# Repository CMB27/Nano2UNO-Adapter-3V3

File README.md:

# Nano2UNO Adapter 3V3

The Nano2UNO Adapter 3V3 is a circuit board to adapt 3.3V Arduino Nano boards the the Arduino UNO form factor.

All the IO pins on the Nano2UNO Adapter 3V3 are wired one to one from the Nano to the UNO form factor, no exceptions.
Pins A6 and A7 of the Nano are not connected because these pins are not present in the UNO form factor.

> [!NOTE]
> This design is distributed WITHOUT ANY EXPRESS OR IMPLIED WARRANTY, INCLUDING OF MERCHANTABILITY, SATISFACTORY QUALITY AND FITNESS FOR A PARTICULAR PURPOSE.
>
> The VCC pin (pin 2) on the ICSP header is connected to 5V.

> [!WARNING]
> Applying voltages higher than 3.3V to any I/O pin could damage any installed 3.3V Arduino Nano board.

### Compatibility
The Nano2UNO Adapter 3V3 should, in theory, be compatible with the following Arduino Nano boards:
- [Arduino Nano 33 IoT](https://store.arduino.cc/collections/boards-modules/products/arduino-nano-33-iot)
- [Arduino Nano 33 BLE](https://store.arduino.cc/collections/boards-modules/products/arduino-nano-33-ble)
- [Arduino Nano 33 BLE Sense](https://store.arduino.cc/collections/boards-modules/products/arduino-nano-33-ble-sense)
- [Arduino Nano 33 BLE Sense Rev2](https://store.arduino.cc/collections/boards-modules/products/nano-33-ble-sense-rev2)
- [Arduino Nano RP2040 Connect](https://store.arduino.cc/collections/boards-modules/products/arduino-nano-rp2040-connect)
- [Arduino Nano ESP32](https://store.arduino.cc/collections/boards-modules/products/nano-esp32)

### Documentation
- [Schematic](Nano2UNO-Adapter-3V3.pdf)
- [KiCAD Source Files](src)
- [STEP 3D Model](extras/Nano2UNO-Adapter-3V3.step)

## Components

### Circuit Board
#### Specifications
- Board Length: __68.58mm__
- Board Width: __53.34mm__
- Board Thickness: __1.6mm__
- Substrate Material: __FR4__
- Copper Layers: __2__
- Copper Thickness: __1oz__
- Soldermask Color: __Any__ (Blue Suggested)
- Smallest Hole Diameter: __0.8mm__
- Smallest Trace Width: __0.2mm__ (7.8mil)
- Smallest Trace Spacing: __0.2mm__ (7.8mil)

#### Suppliers
Below are some circuit board manufacturers I have used in the past.
Generally you will need to upload the upload the [gerber and drill files](gerbers) to their websites in a .zip folder.

- [OSH Park](https://oshpark.com) is a US based circuit board fabrication service.
  They tend to be more expensive than other manufacturers and the number of options they give you are limited (If you use this manufacturer, I hope you like purple).

- [Seeed Studio Fusion](https://www.seeedstudio.com/fusion_pcb.html) makes circuit boards in China.
  They have a lot of options when ordering; please refer to the [specifications](#specifications) above when making your choices.
  They do have a circuit board assembly service as well, but I am not especially familiar with it.

### Purchase Components

| References | Quantity | Manufacturer | Part Number    | Description                     | Notes                                                                                  |
|------------|---------:|--------------|----------------|---------------------------------|----------------------------------------------------------------------------------------|
| C1, C2     |        2 | Panasonic    | ECE-A1HKS100   | 10uF X7R Through-Hole Capacitor | These are use as decoupling capacitors for the 5V DC DC converter.                     |
| D1         |        1 | Vishay       | SB260S-E3/54   | DO-41 Diode                     | This provides reverse voltage protection on the VIN pin and barrel jack.               |
| J1, J3     |        2 | Samtec       | ESW-108-33-L-S | 1x8 Socket Header               | These are extended socket headers that make up part of the Arduino UNO interface.      |
| J2         |        1 | Samtec       | ESW-110-33-L-S | 1x10 Socket Header              | This is an extended socket header that makes up part of the Arduino UNO interface.     |
| J4         |        1 | Samtec       | ESW-106-33-L-S | 1x6 Socket Header               | This is an extended socket header that makes up part of the Arduino UNO interface.     |
| J5, J6     |        2 | Sullins      | PPPC151LFBN-RC	| 1x15 Socket Header              | These are typical, 8.5mm tall, socket headers that make up the Arduino Nano interface. |
| J7         |        1 | TSW/Samtec   | TSW-103-15-L-D | 2x3 Pin Header                  | This is an extended pin header that makes up part of the Arduino UNO interface.        |
| J8         |        1 | CUI          | PJ-102A        | 2.0mm ID, 5.5mm OD Barrel Jack  | This is a pretty common barrel jack.                                                   |
| SW1        |        1 | TE           | 1825910-6      | 6mm Pushbutton Switch           | This is a generic 6mm pushbutton switch.                                               |
| U1         |        1 | RECOM        | R-78K5.0-0.5   | 5V DC DC Converter              | This DC DC converter has an input voltage range of 6.5 - 36V.                          |

#### Suppliers
Below are some electronics suppliers I have used in the past:

- [Digi-Key](https://www.digikey.com/) is my usual go-to supplier for electronic components.
  Their website makes it pretty easy to sort through parts.

- [Mouser](https://www.mouser.com/) is very similar to Digi-Key in a lot of ways.
  They sometimes have better pricing, and they have excellent customer support.

- [Newark](https://www.newark.com/) tends to have a bit different selection than Digi-Key and Mouser, especially in the area of connectors.

- [Octopart](https://octopart.com/) is not a supplier per se; it is essenitally an electronic component search engine.
  This can be a very helpful tool when looking for parts, especially somewhat unusual ones, like extended socket headers.

All of these suppliers have a feature on their respective websites where you can upload a spreadsheet file, such as [Nano2UNO-Adapter-3V3-BOM.csv](Nano2UNO-Adapter-3V3-BOM.csv), to populate the cart or find parts.

Last I checked, it is not possible to order all the components needed to build a Nano2UNO Adapter 3V3 from just one of these suppliers. Multiple orders will be needed.

## Assembly

### Tools and Supplies
| Item              | Optional | Notes                                                                                                                                              |
|-------------------|----------|----------------------------------------------------------------------------------------------------------------------------------------------------|
| Soldering Iron    | No       | Make sure you use a good quality soldering iron. A poor quality soldering iron will give you a miserable soldering experience.                     |
| Flush Cutters     | No       | These are used to trim component leads.                                                                                                            |
| Flux Core Solder  | No       | Leaded solder is easier to work with, but lead-free solder is better for the environment.                                                          |
| Solder Flux       | Yes      | Extra flux will make the solder flow better. I don't usually use it when through-hole soldering, but it can be helpful.                            |
| Solder Wick       | Yes      | This is used to remove solder from places you don't want it.                                                                                       |
| Solder Sucker     | Yes      | If you need to de-solder a component, this, along with solder wick, is the tool you want. This can quickly remove most of the solder from a joint. |
| Arduino Shield    | Yes      | This can be used to hold the stacking socket headers in place while being assembled.                                                               |
| Isopropyl Alcohol | Maybe    | This is used to remove flux. It is not needed if you are using no-clean flux.                                                                      |
| Dish Soap         | Maybe    | This is used to remove flux residue. It is not needed if you are using no-clean flux.                                                              |

> **Note on Flux**  
> Traditional flux if left on the assembled circuit board could cause some serious issues.
> It can potentially cause shorts or significant [parasitic capacitance](https://en.wikipedia.org/wiki/Parasitic_capacitance).
> It is also somewhat corrosive and can, over time, damage your circuit board.
> This sort of flux must be cleaned off the board after assembly.
> 
> To address these issues there are no-clean fluxes, that can be left on the circuit board assembly and are unlikly to cause these issues.
> There are also water-soluble fluxes that can be cleaned off with hot water, though I have found that some isopropyl alcohol can speed up the process.
> There are also fluxes that are both no-clean and water soluble; this is what I like to use.

### Assembly Steps
All the components are placed on the front side of the board and solderd on the back side of the board.
These steps go through soldering each component, starting with the shortest.

> The [interactive HTML BOM](https://github.com/CMB27/Nano2UNO-Adapter-3V3/blob/main/extras/Nano2UNO-Adapter-3V3-interactive-BOM.html) may be helpful to you in this process.
> It graphically shows where each component goes on the board.
> You will need to download it in order to view it; GitHub does not render HTML files in repositories.

#### 1. D1 (Diode)
- Bend the diode leads so that the part will fit in the footprint.
- Place the diode, ensuring that the side with the line closest to it (the cathode) is facing the squarish pad.
- Bend the diode leads on the backside of the board to ensure the diode remains in place when soldering.
- Solder the leads to the pads.
- Trim the leads using flush cutters.

#### 2. SW1 (Pushbutton Switch)
- Place the switch; it should stay in place.
- Solder the leads to the board.

#### 3. C1-C2 (Capacitors)
- Place the capacitors, ensuring that the `-` symbol on the capacitors is facing away from the `+` symbols on the board.
  For the capacitors the, the positive lead goes through the squarish pad and the negative lead goes through the circular pad.
- Bend the capacitor leads on the backside of the board to ensure the capacitors stay in place.
- Solder the capacitor leads.
- Trim the leads.

#### 4. J5-J6 (Arduino Nano Socket)
- If you have an Arduino Nano board, place the socket headers on the Nano's pins, then place the socket header pins through the holes on the Nano2UNO circuit board.
  This will ensure your Nano board will line up with the sockets once they are soldered in place.
  If you do not have an Arduino Nano board on hand, place the socket header pins as precisely as you can.
- Carefully flip the board over the board, holding the socket headers in place.
  This can be difficult; it may be necessary to solder each socket header one at a time.
- Tack solder the end pins of the socket headers.
- Check that the socket headers are straight and seated correctly.
  If necessary remelt the solder joints to adjust the socket headers. (This is where flux can be nice.)
- Once the headers are straight, solder the remaining pins. I usually go every other pin to avoid heat build up, then go back soldering the pins I skipped.
- If you used an Arduino Nano board to place the sockets, remove it now.

#### 5. U1 (DC DC Converter)
- Place the DC DC converter module.
- Tack solder one pin. I like to solder the middle pin.
- Check that the component is straight and seated correctly.
  Remelt the tack joint to make corrections if necessary.
- Solder the remaining two pins.

#### 6. J8 (Barrel Jack)
- Place the barrel Jack.
- Tack solder the pin near the middle of the component.
- Check that the part is straight and seated correctly.
- Solder the remaining pins.

#### 7. J7 (ICSP Header)
- Place the pin header.
- Tack solder one pin. I like to solder one of the corners.
  Be careful when soldering this component; it has a lot of exposed metal that can burn you when heated by a soldering iron.
- Check that the part is straight and seated correctly.
- Solder the remaining pins.

#### 8. J1-J4 (Arduino UNO Interface)
- If you have a shield for the Arduino UNO, place the socket headers on its pins, then place the socket header pins through the holes on the Nano2UNO circuit board.
  This will make it easier and faster to install the sockets.
  If you don't have a shield you will likely need to install the sockets one at a time.
- Carefully flip the board over the board, holding the socket headers in place.
- Tack solder the end pins of the socket headers.
- Check that the socket headers are straight and seated correctly.
- Once the headers are straight, solder the remaining pins.
- If you used a shield, remove it now.

#### 9. Clean Flux Off Board  
_If you used no-clean flux, you can skip this step._

> [!NOTE]
> This step was written with water-soluble flux in mind.  
> If you used non-water-soluble flux, you may need to use a different cleaning process.

- Use isopropyl alcohol with a toothbrush to remove the bulk of the flux.
- Clean the board with dish soap and warm water using the same toothbrush.
- Dry the board thoroughly. I like to use compressed air for this step.

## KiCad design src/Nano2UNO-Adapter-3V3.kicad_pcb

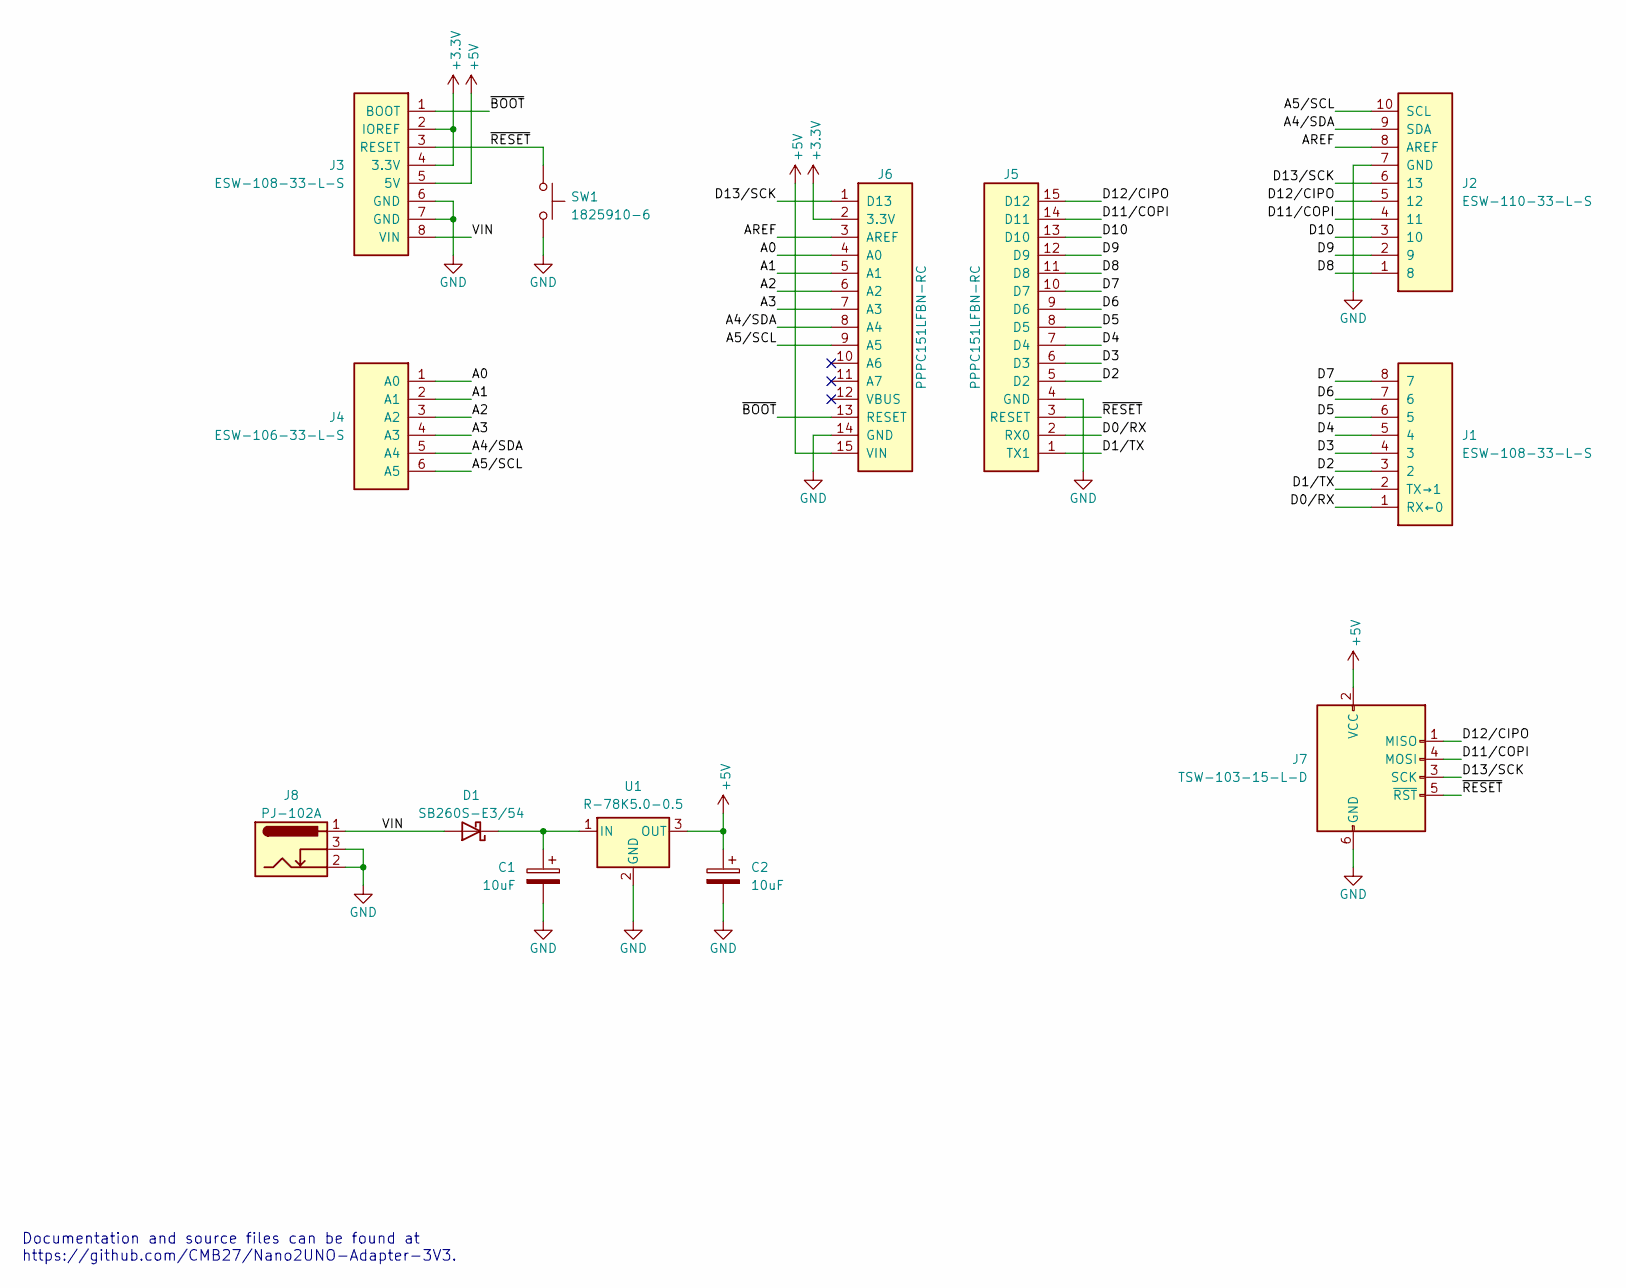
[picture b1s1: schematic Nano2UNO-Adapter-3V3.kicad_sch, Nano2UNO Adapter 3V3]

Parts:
C1, C2: 10uF; CP_Radial_D6.3mm_P2.50mm; Part Number ECE-A1HKS100
D1: SB260S-E3/54; D_DO-41_SOD81_P10.16mm_Horizontal; Part Number SB260S-E3/54
J1: ESW-108-33-L-S; PinSocket_1x08_P2.54mm_Vertical_UNO_Digital_1; Part Number ESW-108-33-L-S
J2: ESW-110-33-L-S; PinSocket_1x10_P2.54mm_Vertical_UNO_Digital_2; Part Number ESW-110-33-L-S
J3: ESW-108-33-L-S; PinSocket_1x08_P2.54mm_Vertical_UNO_Power; Part Number ESW-108-33-L-S
J4: ESW-106-33-L-S; PinSocket_1x06_P2.54mm_Vertical_UNO_Analog; Part Number ESW-106-33-L-S
J5: PPPC151LFBN-RC; PinSocket_1x15_P2.54mm_Vertical_Nano_1; Part Number PPPC151LFBN-RC
J6: PPPC151LFBN-RC; PinSocket_1x15_P2.54mm_Vertical_Nano_2; Part Number PPPC151LFBN-RC
J7: TSW-103-15-L-D; PinHeader_2x03_P2.54mm_Vertical_UNO_ICSP; Part Number TSW-103-15-L-D
J8: PJ-102A; BarrelJack_CUI_PJ-102A_Horizontal; Part Number PJ-102A
SW1: 1825910-6; SW_PUSH_6mm_Reset; Part Number 1825910-6
U1: R-78K5.0-0.5; Part Number R-78K5.0-0.5

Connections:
+3V3: J3.2 (IOREF), J3.4 (3.3V), J6.2 (3.3V)
+5V: C2.1, J3.5 (5V), J6.15 (VIN), J7.2 (VCC), U1.3 (OUT)
/A0: J4.1 (A0), J6.4 (A0)
/A1: J4.2 (A1), J6.5 (A1)
/A2: J4.3 (A2), J6.6 (A2)
/A3: J4.4 (A3), J6.7 (A3)
/A4/SDA: J2.9 (SDA), J4.5 (A4), J6.8 (A4)
/A5/SCL: J2.10 (SCL), J4.6 (A5), J6.9 (A5)
/AREF: J2.8 (AREF), J6.3 (AREF)
/D0/RX: J1.1 (RX←0), J5.2 (RX0)
/D1/TX: J1.2 (TX→1), J5.1 (TX1)
/D2: J1.3 (2), J5.5 (D2)
/D3: J1.4 (3), J5.6 (D3)
/D4: J1.5 (4), J5.7 (D4)
/D5: J1.6 (5), J5.8 (D5)
/D6: J1.7 (6), J5.9 (D6)
/D7: J1.8 (7), J5.10 (D7)
/D8: J2.1 (8), J5.11 (D8)
/D9: J2.2 (9), J5.12 (D9)
/D10: J2.3 (10), J5.13 (D10)
/D11/COPI: J2.4 (11), J5.14 (D11), J7.4 (MOSI)
/D12/CIPO: J2.5 (12), J5.15 (D12), J7.1 (MISO)
/D13/SCK: J2.6 (13), J6.1 (D13), J7.3 (SCK)
/VIN: D1.2 (A), J3.8 (VIN), J8.1
/~BOOT: J3.1 (BOOT), J6.13 (RESET)
/~RESET: J3.3 (RESET), J5.3 (RESET), J7.5 (~RST), SW1.2
GND: C1.2, C2.2, J2.7 (GND), J3.6 (GND), J3.7 (GND), J5.4 (GND), J6.14 (GND), J7.6 (GND), J8.2, J8.3, SW1.1, U1.2 (GND)
unnamed: C1.1, D1.1 (K), U1.1 (IN)

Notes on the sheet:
Documentation and source files can be found at https://github.com/CMB27/Nano2UNO-Adapter-3V3.

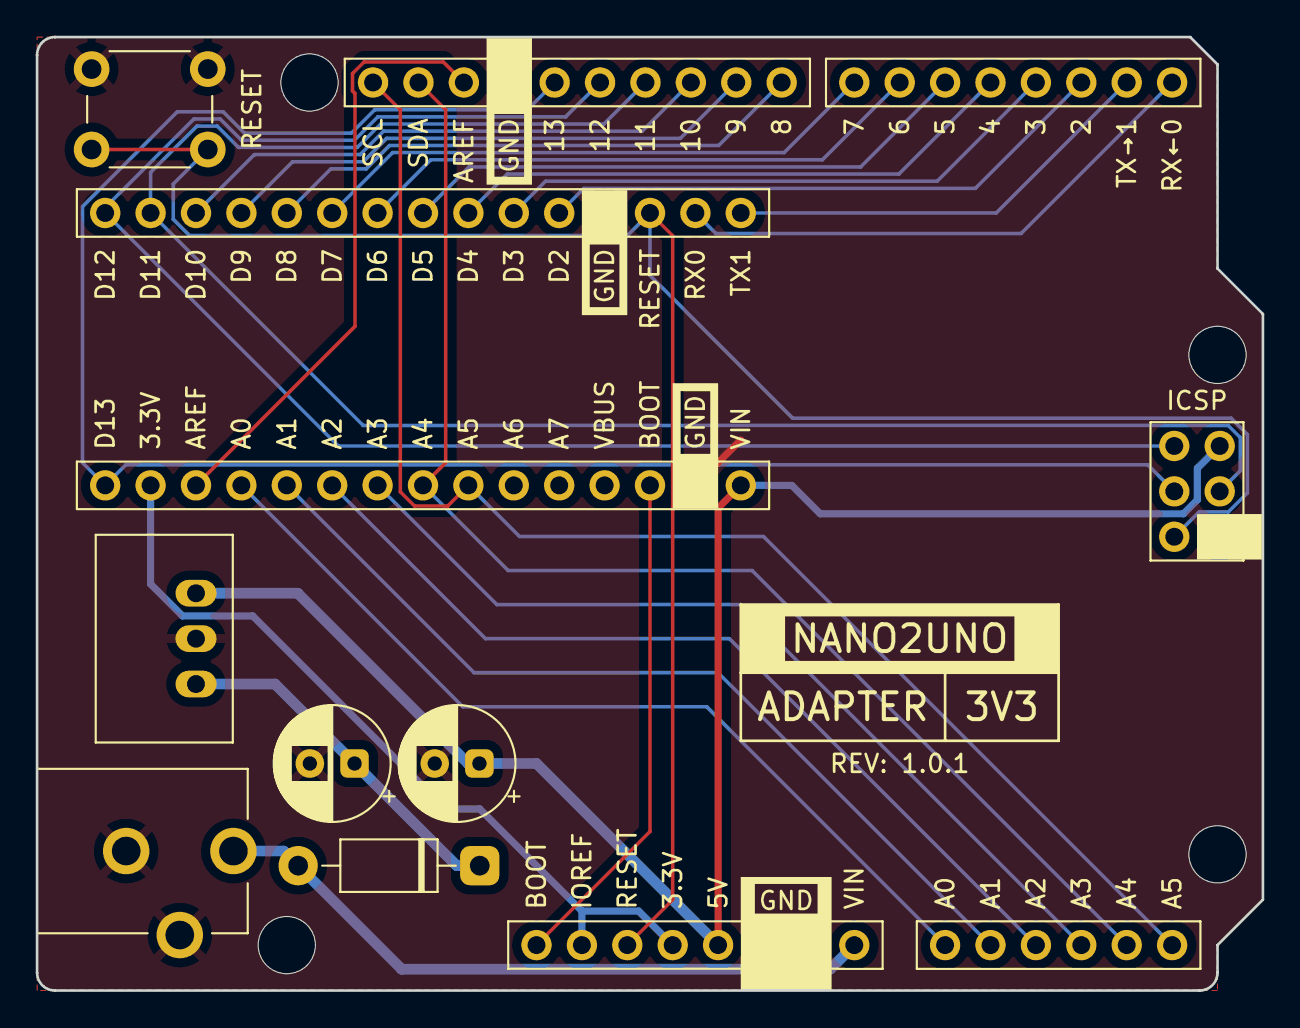
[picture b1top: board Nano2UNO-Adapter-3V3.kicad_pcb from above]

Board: 2 copper layers, 68.6 x 53.3 mm, 17 parts (0 on the bottom side), 28 nets.

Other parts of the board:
MH1, MH2, MH3, MH4: MountingHole_3.2mm

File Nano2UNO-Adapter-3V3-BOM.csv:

"Item","References","Quantity","Manufacturer","Part Number","Description"

"1","","1","","","Nano2UNO Adapter 3V3 Bare Circuit Board"
"2","C1, C2","2","Panasonic","ECE-A1HKS100 ","10uF X7R Through-Hole Capacitor"
"3","D1","1","Vishay","SB260S-E3/54","DO-41 Diode"
"4","J1, J3","2","Samtec","ESW-108-33-L-S","1x8 Socket Header"
"5","J2","1","Samtec","ESW-110-33-L-S","1x10 Socket Header"
"6","J4","1","Samtec","ESW-106-33-L-S","1x6 Socket Header"
"7","J5, J6","2","Sullins","PPPC151LFBN-RC","1x15 Socket Header"
"8","J7","1","TSW/Samtec","TSW-103-15-L-D","2x3 Pin Header"
"9","J8","1","CUI","PJ-102A","2.0mm ID, 5.5mm OD Barrel Jack"
"10","SW1","1","TE","1825910-6","6mm Pushbutton Switch"
"11","U1","1","RECOM","R-78K5.0-0.5","5V DC DC Converter"

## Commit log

2023-12-06 Increased the font size of the comments and dimensions.
2023-12-06 Genereated images of board.
2023-12-06 Removed the board PDF. Updated the schematic PDF.
2023-12-06 Updated README.
2023-12-06 Updated README. Resized images.
2023-12-06 Generated interactive html BOM.
2023-12-06 Fixed BOM
2023-12-09 Generated step file of board assembly.
2023-12-09 Update README.md
    Added assembly steps.
2023-12-09 Update README.md
    Fixed several spelling errors.
2023-12-17 Added photographs of completed board.
2023-12-17 Linked to photograph instead of rendered view to README. Added disclaimer of warranties note to README. Added note about 5V on ICSP header to README.
2023-12-17 Changed revision number from 0.0.1 to 1.0.0
2023-12-17 Update README.md
    Consolidated notes into a single note.
2023-12-26 Update README.md
    Fixed a spelling error.
2023-12-30 Updated the README.
2023-12-31 Updated the socket 3D models to have more detail. Consolidated the 3D model notes into one file.
2023-12-31 Added additional part metadata to the schematic. Changed RST to RESET on one of the schematic symbols. Changed the revision from 1.0.0 to 1.0.1.
2023-12-31 Tweaked the BOM.
2023-12-31 Regenerated a PDF of the schematic.
2023-12-31 Regenerated gerber and drill files.
2023-12-31 Regenerated interactive BOM and STEP file of assembly.
2023-12-31 Added production file generation instructions.

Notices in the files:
src/Nano2UNO-Adapter-3V3.kicad_pcb:
© 2023 C. M. Bulliner. Released under the CERN-OHL-P v2 license.
LICENSED UNDER CERN-OHL-P V2
